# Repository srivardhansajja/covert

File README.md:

# Covert Communications Device

## UIUC ECE 445 Senior Design / Capstone Project

Won Best Engineered Project Award, and permanently listed in the [Hall of Fame](https://courses.engr.illinois.edu/ece445/hall-of-fame.asp) for Spring 2021

## Abstract

The primary purpose of this project is to provide a means for safe and effective communication in highly sensitive military and law-enforcement operations.

It is important for a two-way channel of communication to exist between the base and individuals in the field. Regular communication tools have output which can disrupt sensory awareness of the user thereby rendering them unsuitable for information transmission in these situations. A wearable device thatrelays messages that are only detectable by the user, and that will not affect their focus is the purpose of this project.

The final output of this project is a small device that can be installed on the human body in a convenient location, such as the upper arm or the outer thigh. The user should be able to access the device using their hand. The device will transmit information to the user through the cadence of haptic feedback (vibration patterns). The user will also be able to transmit information to all other devices in near real-time using a button on the device (pressing the button with whatever cadence is required, e.g. long-short-short). Team selected codes can be established to effectively transmit complex information or instructions.

## Prototype

## Block Diagram

## Documents
- [Project Report](https://courses.engr.illinois.edu/ece445/getfile.asp?id=19398)
- [Design Document](https://courses.engr.illinois.edu/ece445/getfile.asp?id=19192)
- [Proposal](https://courses.engr.illinois.edu/ece445/getfile.asp?id=18686)

## Software
- STM32 CubeIDE development, LoRa radio communications + crypto libraries

## Board
- Eagle schematic + board files 
- CAD casing layout
- Gerber files

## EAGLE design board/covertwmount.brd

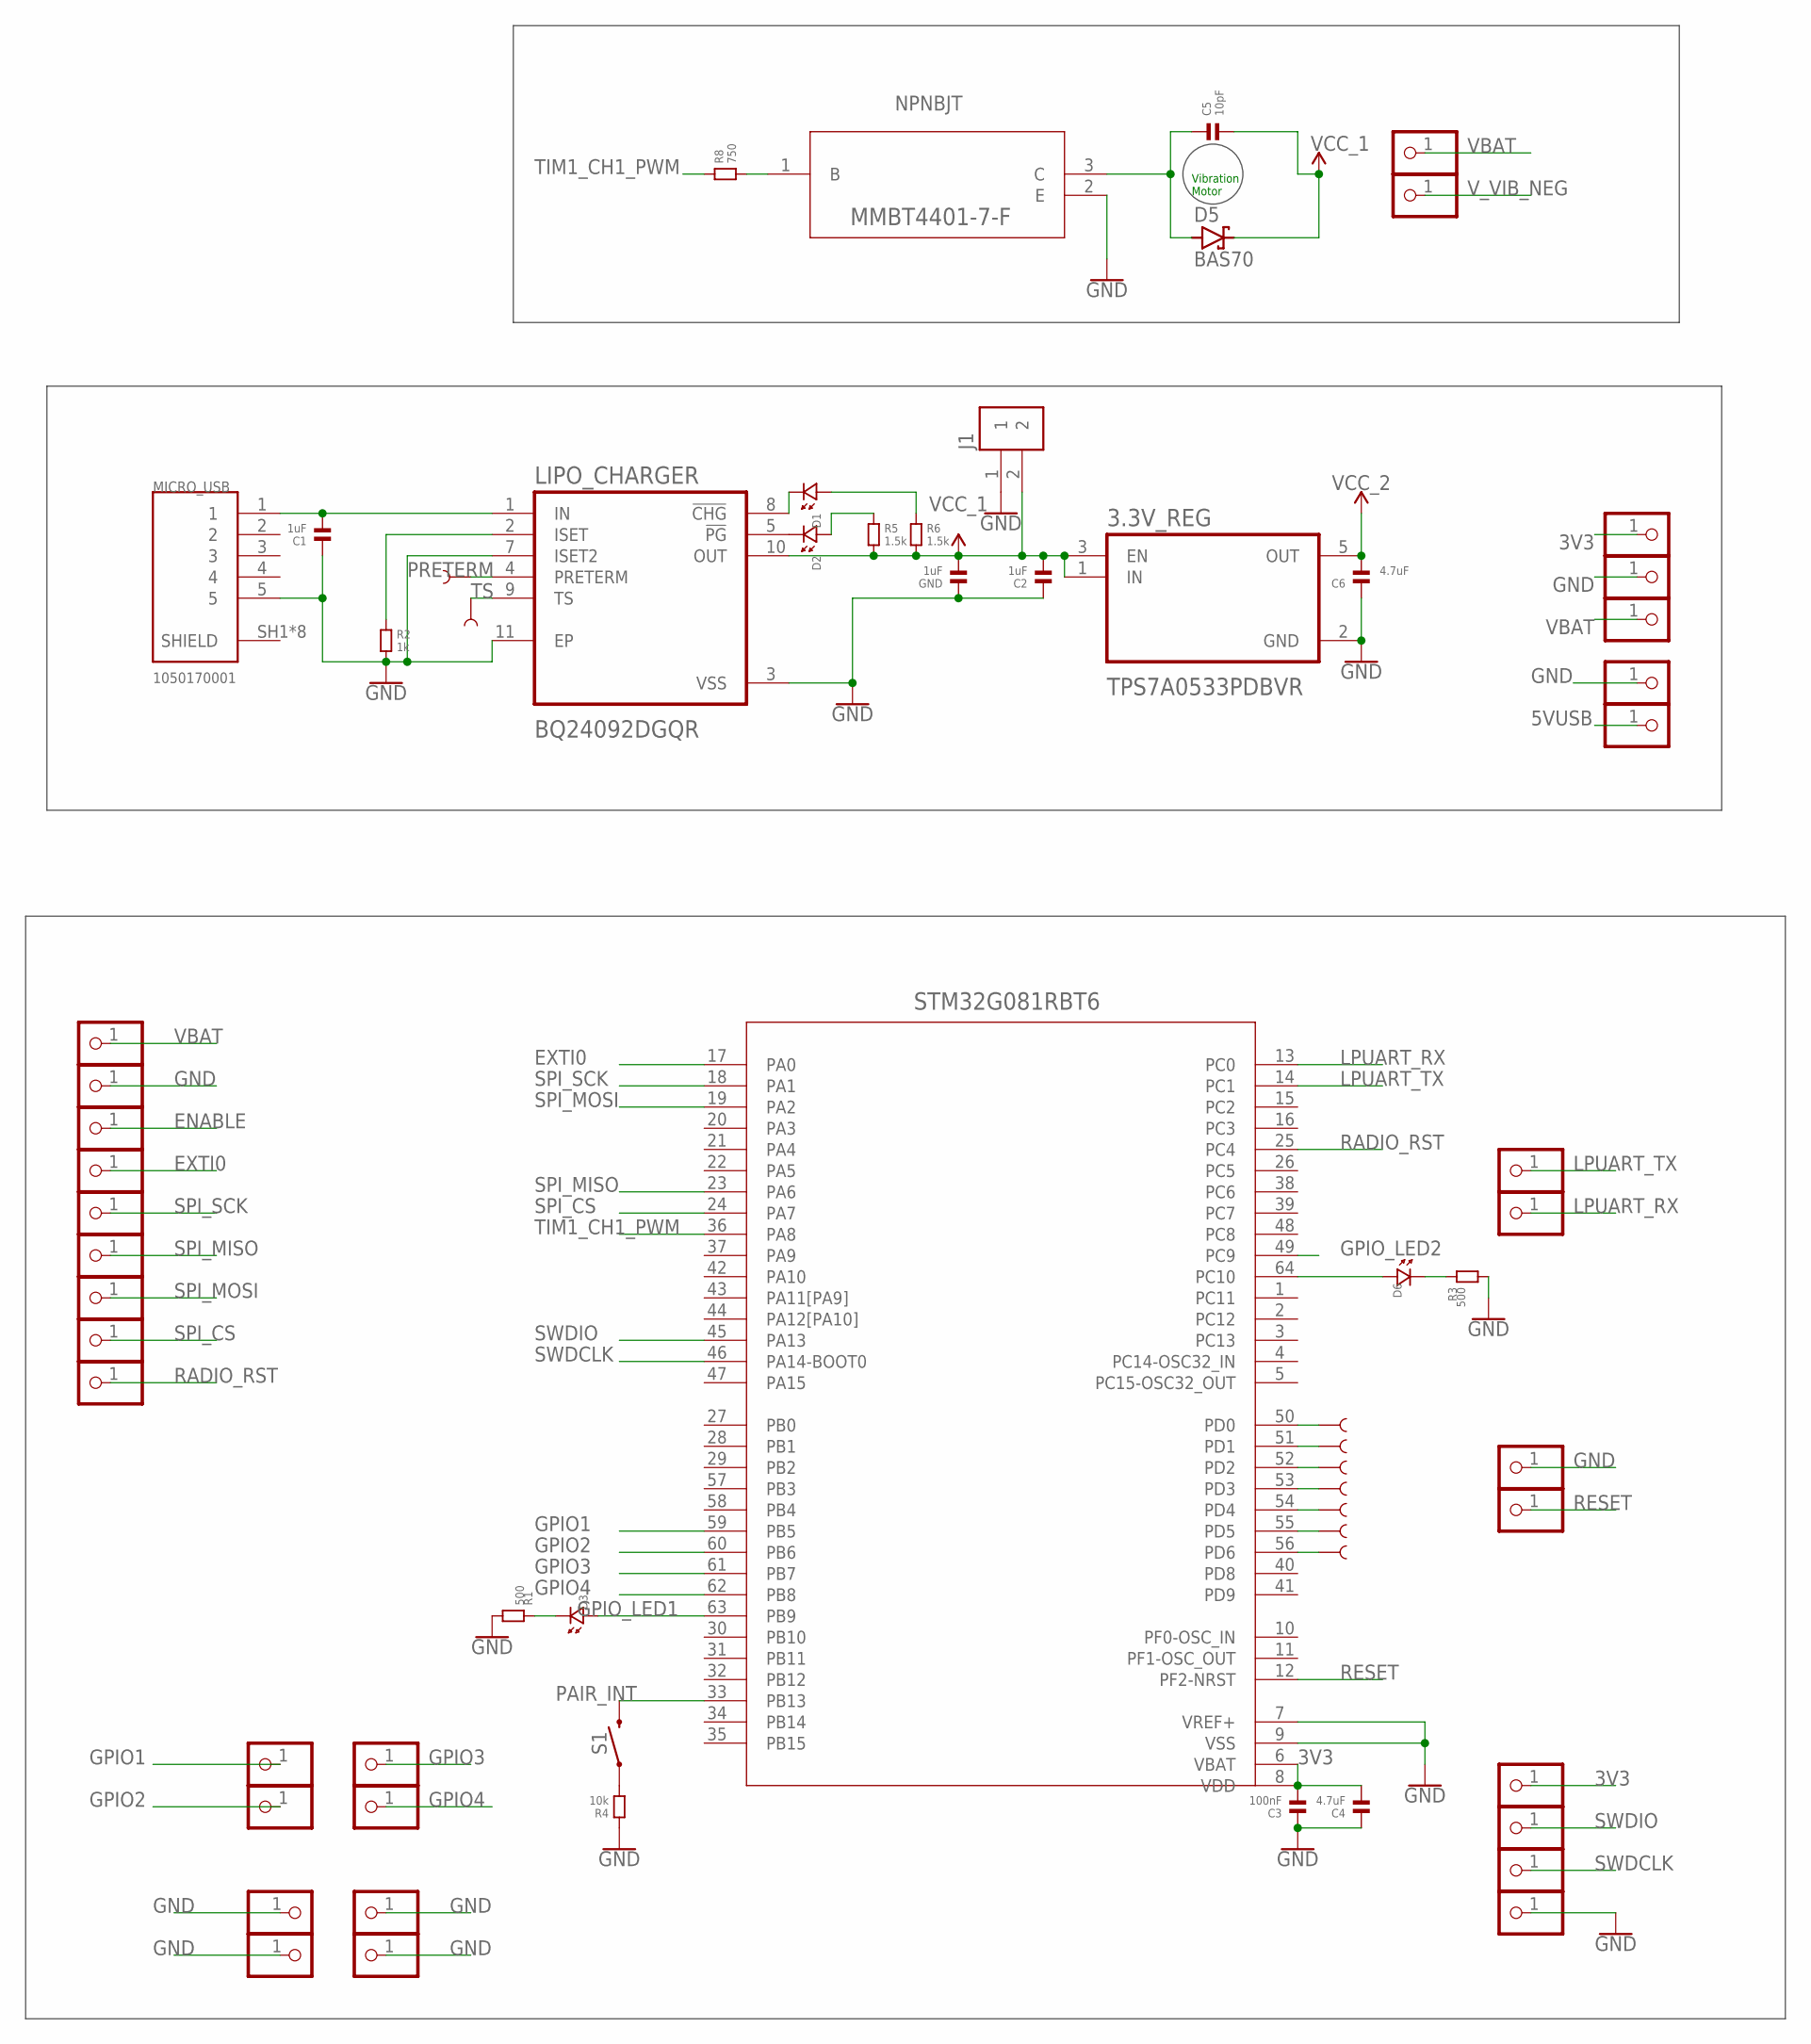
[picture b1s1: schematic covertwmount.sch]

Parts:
3.3V_REG: TPS7A0533PDBVR; SOT95P280X145-5N
C1, C2: 1uF; 0805
C3: 100nF; 0805
C4, C6: 4.7uF; 0805
C5: 10pF; 0805
D1, D2, D3, D6: LED.0805; 0805.LED
D5: BAS70; SOT23
GND: 1uF; 0805
J1: B2B-PH-K-S(LF)(SN); JST_B2B-PH-K-S(LF)(SN)
JP1, JP2, JP3, JP4, JP5, JP6, JP7, JP8, JP9, JP10, JP11, JP12, JP13, JP14, JP15, JP16, JP17, JP18, JP19, JP20, JP21, JP22, JP23, JP24, JP26, JP27, JP28, JP29, JP30, JP31, JP32, JP33: PINHD-1X1; 1X01
LIPO_CHARGER: BQ24092DGQR; IC_XTR111AIDGQR
MICRO_USB: 1050170001; MOLEX_1050170001
R1, R3: 500; 0805
R2: 1k; 0805
R4: 10k; 0805
R5, R6: 1.5k; 0805
R8: 750; 0805
S1: MOMENTARY-SWITCH-SPST-PTH-6.0MM; TACTILE_SWITCH_PTH_6.0MM
TP1, TP2, TP3, TP4, TP5, TP6, TP7, TP8, TP9: TEST-POINT2; PAD.02X.02
U1: STM32G081RBT6; LQFP-64
U2: MMBT4401-7-F; SOT-23_DIO

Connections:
3V3: 3.3V_REG.5 (OUT), C3.2, C4.2, C6.2, JP4.1, JP16.1, U1.6 (VBAT), U1.8 (VDD)
5VUSB: C1.2, JP30.1, LIPO_CHARGER.1 (IN), MICRO_USB.1
ENABLE: JP11.1
EXTI0: JP10.1, U1.17 (PA0)
GND: 3.3V_REG.2 (GND), C1.1, C2.1, C3.1, C4.1, C6.1, GND.1, J1.1, JP3.1, JP12.1, JP15.1, JP23.1, JP26.1, JP27.1, JP28.1, JP29.1, JP33.1, LIPO_CHARGER.3 (VSS), LIPO_CHARGER.7 (ISET2), LIPO_CHARGER.11 (EP), MICRO_USB.5, R1.1, R2.2, R3.1, R4.1, U1.7 (VREF+), U1.9 (VSS), U2.2 (E)
GPIO1: JP19.1, U1.59 (PB5)
GPIO2: JP20.1, U1.60 (PB6)
GPIO3: JP17.1, U1.61 (PB7)
GPIO4: JP18.1, U1.62 (PB8)
GPIO_LED1: D3.P$1 (1), U1.63 (PB9)
GPIO_LED2: D6.P$1 (1), U1.64 (PC10)
LPUART_RX: JP32.1, U1.13 (PC0)
LPUART_TX: JP31.1, U1.14 (PC1)
unnamed: LIPO_CHARGER.2 (ISET), R2.1
unnamed: D6.P$2 (2), R3.2
unnamed: D3.P$2 (2), R1.2
unnamed: D2.P$1 (1), R5.1
unnamed: D1.P$1 (1), R6.1
unnamed: D2.P$2 (2), LIPO_CHARGER.5 (!PG)
unnamed: R8.2, U2.1 (B)
unnamed: R4.2, S1.1
unnamed: D1.P$2 (2), LIPO_CHARGER.8 (!CHG)
PAIR_INT: S1.3 (2), U1.33 (PB13)
PD0: TP3.P$1, U1.50 (PD0)
PD1: TP4.P$1, U1.51 (PD1)
PD2: TP5.P$1, U1.52 (PD2)
PD3: TP6.P$1, U1.53 (PD3)
PD4: TP7.P$1, U1.54 (PD4)
PD5: TP8.P$1, U1.55 (PD5)
PD6: TP9.P$1, U1.56 (PD6)
PRETERM: LIPO_CHARGER.4 (PRETERM), TP2.P$1
RADIO_RST: JP5.1, U1.25 (PC4)
RESET: JP24.1, U1.12 (PF2-NRST)
SPI_CS: JP6.1, U1.24 (PA7)
SPI_MISO: JP8.1, U1.23 (PA6)
SPI_MOSI: JP7.1, U1.19 (PA2)
SPI_SCK: JP9.1, U1.18 (PA1)
SWDCLK: JP2.1, U1.46 (PA14-BOOT0)
SWDIO: JP1.1, U1.45 (PA13)
TIM1_CH1_PWM: R8.1, U1.36 (PA8)
TS: LIPO_CHARGER.9 (TS), TP1.P$1
VBAT: 3.3V_REG.1 (IN), 3.3V_REG.3 (EN), C2.2, C5.2, D5.3 (C), GND.2, J1.2, JP13.1, JP14.1, JP21.1, LIPO_CHARGER.10 (OUT), R5.2, R6.2
V_VIB_NEG: C5.1, D5.1 (A), JP22.1, U2.3 (C)

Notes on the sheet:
Vibration Motor

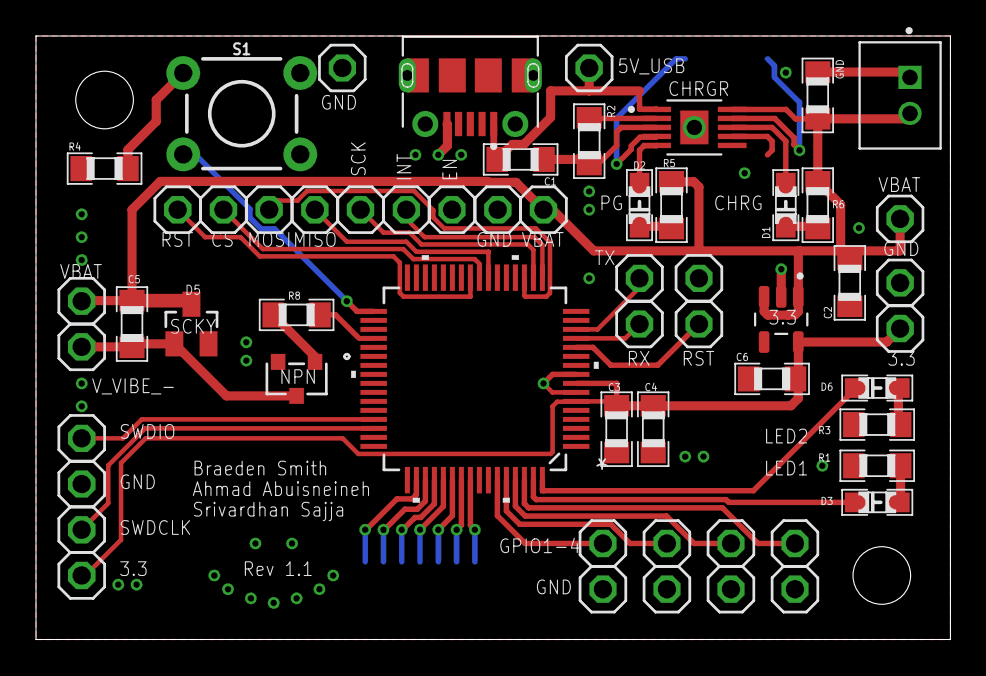
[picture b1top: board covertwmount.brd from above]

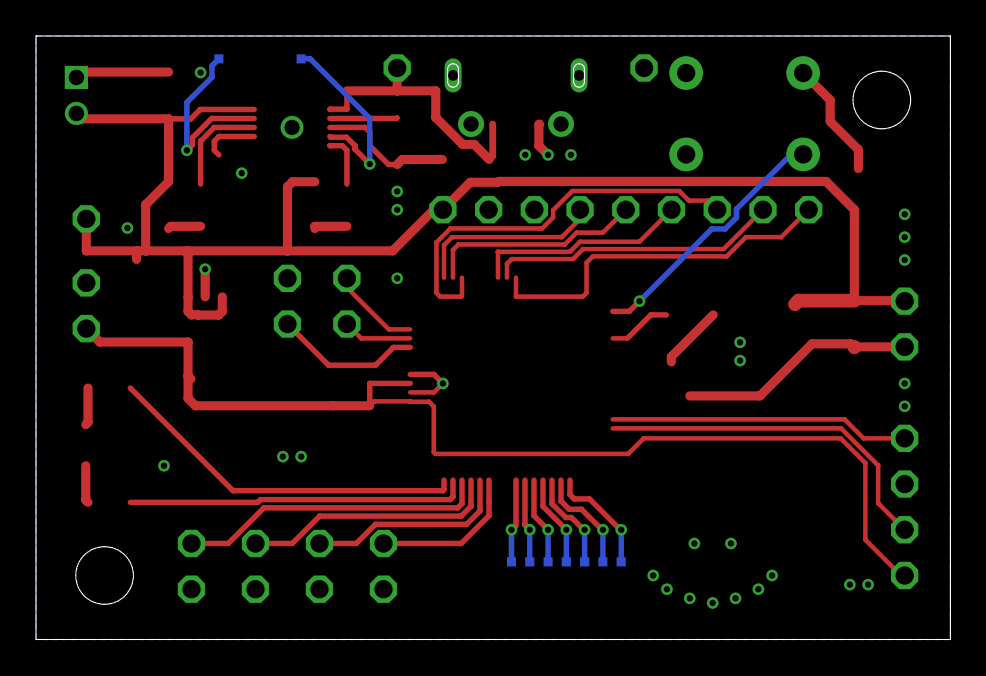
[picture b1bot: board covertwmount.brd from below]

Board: 2 copper layers, 50.8 x 33.5 mm, 67 parts (9 on the bottom side), 42 nets.

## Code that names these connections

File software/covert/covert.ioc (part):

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Mcu.Name=STM32G081RBTx
Mcu.Package=LQFP64
Mcu.UserName=STM32G081RBTx
PA0.GPIOParameters=GPIO_PuPd,GPIO_Label,GPIO_ModeDefaultEXTI
PA0.GPIO_Label=RADIO_INT
PA0.GPIO_ModeDefaultEXTI=GPIO_MODE_IT_RISING
PA0.GPIO_PuPd=GPIO_PULLDOWN
PA0.Signal=GPXTI0
PA1.Mode=Full_Duplex_Master
PA1.Signal=SPI1_SCK
PA13.Mode=Serial_Wire
PA13.Signal=SYS_SWDIO
PA14-BOOT0.Mode=Serial_Wire
PA14-BOOT0.Signal=SYS_SWCLK
PA2.Mode=Full_Duplex_Master
PA2.Signal=SPI1_MOSI
PA6.Mode=Full_Duplex_Master
PA6.Signal=SPI1_MISO
PA7.GPIOParameters=GPIO_PuPd,GPIO_Label
PA7.GPIO_Label=RADIO_CS
PA7.GPIO_PuPd=GPIO_PULLUP
PA7.Signal=GPIO_Output
PA8.GPIOParameters=GPIO_Label
PA8.GPIO_Label=VIBE_PWM
PA8.Signal=S_TIM1_CH1
PB13.GPIOParameters=GPIO_PuPd,GPIO_Label,GPIO_ModeDefaultEXTI
PB13.GPIO_Label=PAIR
PB13.GPIO_ModeDefaultEXTI=GPIO_MODE_IT_FALLING
PB13.GPIO_PuPd=GPIO_PULLUP
PB13.Signal=GPXTI13
PB8.GPIOParameters=GPIO_PuPd,GPIO_Label,GPIO_ModeDefaultEXTI
PB8.GPIO_Label=VIBE_BUTTON
PB8.GPIO_ModeDefaultEXTI=GPIO_MODE_IT_RISING_FALLING
PB8.GPIO_PuPd=GPIO_PULLUP
PB8.Signal=GPXTI8
PB9.GPIOParameters=GPIO_Label
PB9.GPIO_Label=LED1
PB9.Signal=GPIO_Output
PC10.GPIOParameters=GPIO_Label
PC10.GPIO_Label=LED2
PC10.Signal=GPIO_Output
PC4.GPIOParameters=GPIO_Label
PC4.GPIO_Label=RADIO_RESET
PC4.Signal=GPIO_Output
RCC.HSE_VALUE=8000000
RCC.SYSCLKFreq_VALUE=64000000
RCC.SYSCLKSource=RCC_SYSCLKSOURCE_PLLCLK
board=custom

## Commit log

2021-08-05 committed all files

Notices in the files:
parts and their libraries:
SparkFun-Switches: Licensing: Creative Commons ShareAlike 4.0 International - https://creativecommons.org/licenses/by-sa/4.0
COPYRIGHT: Copyright (C) 2018 Accelerated Designs. All rights reserved
